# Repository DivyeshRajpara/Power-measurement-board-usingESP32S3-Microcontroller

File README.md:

# Power-measurement-board-usingESP32S3-Microcontroller
This project involves the development of a power-measurement board designed using KiCad and programmed with the ESP32-S3 microcontroller. The board measures electrical power and transmits the data via BLE to a mobile device. The project includes KiCad design files, ESP32-S3 firmware, and a mobile app interface for real-time data monitoring.
components
Hardware: KiCad design files for the power measurement board.
Firmware: ESP32-S3 code for data acquisition and BLE communication.
Devices: Interface for displaying real-time power data on a mobile device.
features
Power Measurement: Accurate measurement of voltage, current, and power.
Bluetooth Low Energy: Wireless data transmission to mobile devices.
ESP32-S3 Microcontroller: High-performance MCU with integrated Wi-Fi and BLE.
KiCad Design: Open-source PCB design with comprehensive schematics and layout files.

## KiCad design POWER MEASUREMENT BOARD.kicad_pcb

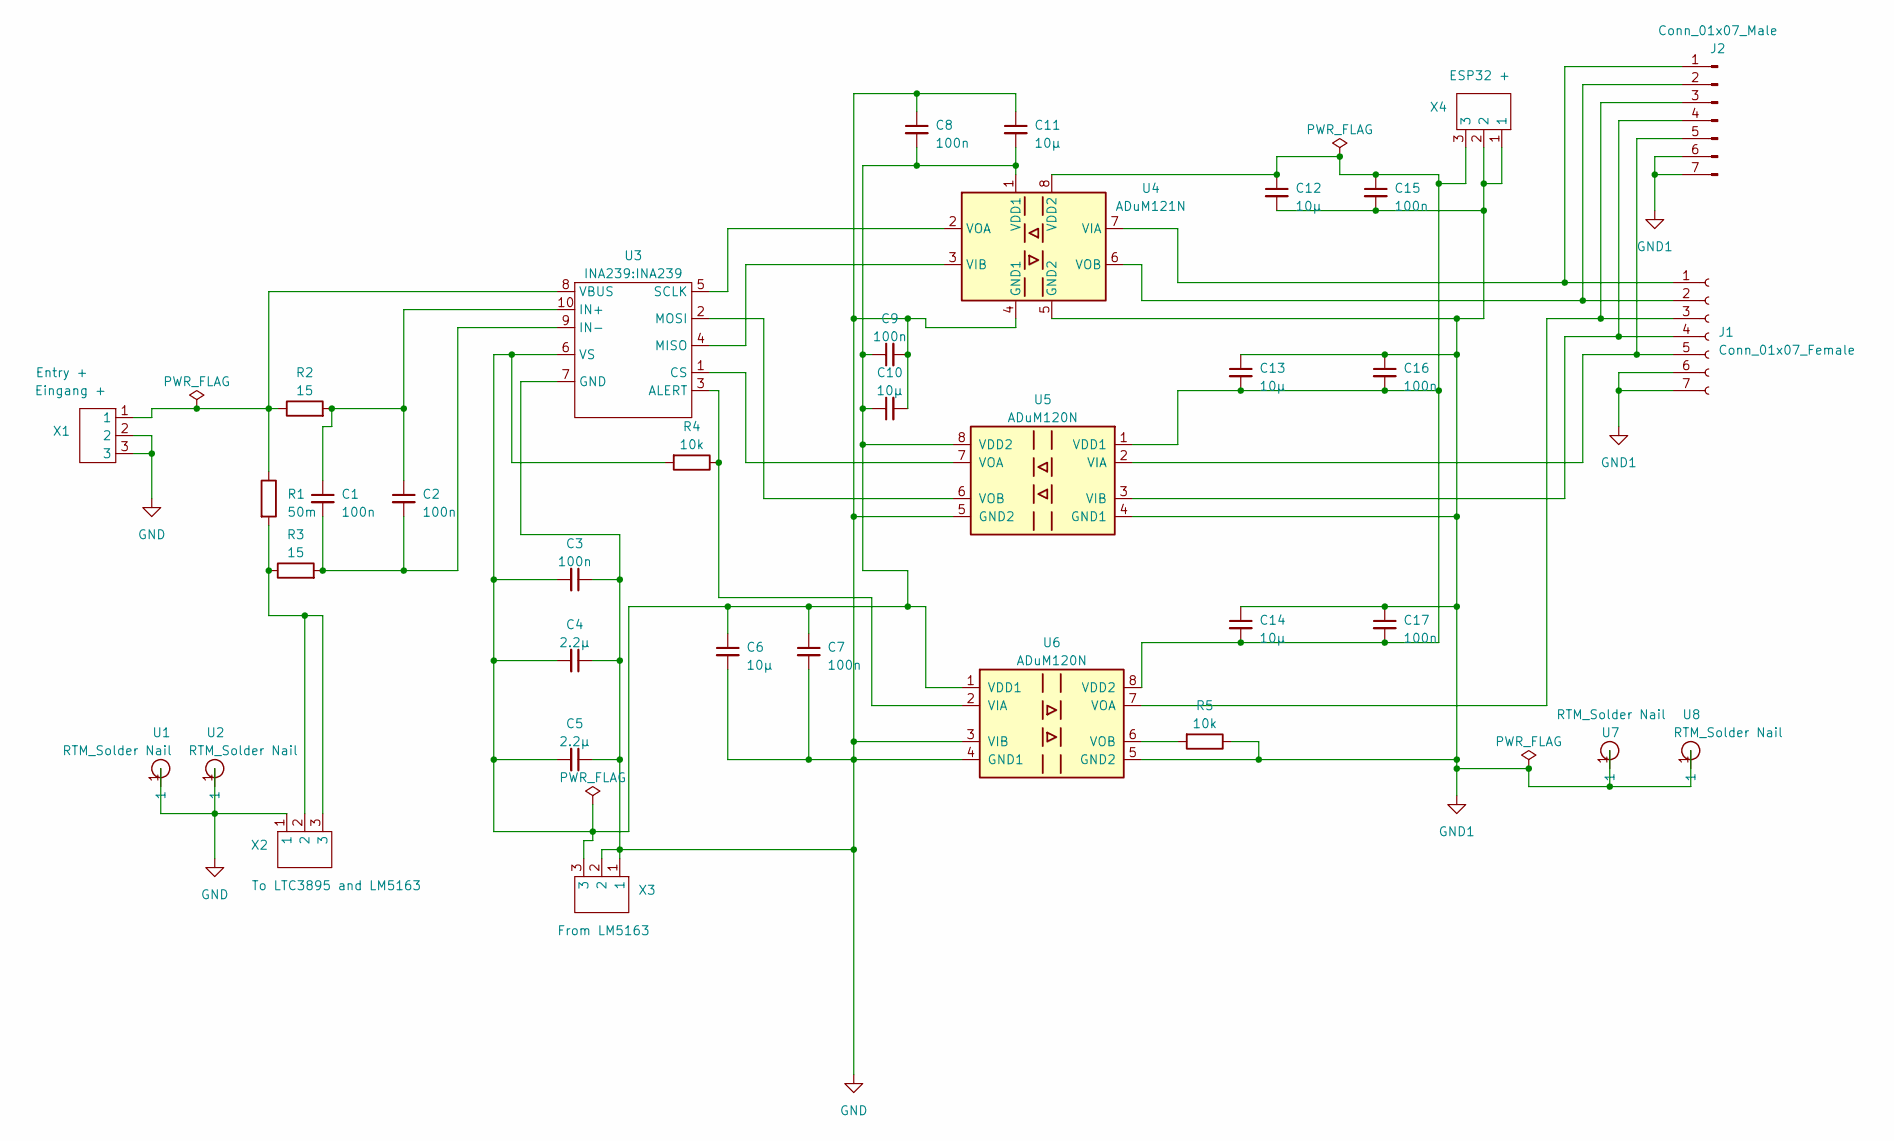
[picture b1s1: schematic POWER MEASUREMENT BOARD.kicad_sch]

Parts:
C1, C2, C15, C16, C17: 100n; C_0402_1005Metric_Pad0.74x0.62mm_HandSolder
C3, C7, C8, C9: 100n; C_0805_2012Metric_Pad1.18x1.45mm_HandSolder
C4, C5: 2.2μ; C_1206_3216Metric_Pad1.33x1.80mm_HandSolder
C6, C10, C11, C12, C13, C14: 10μ; C_1206_3216Metric_Pad1.33x1.80mm_HandSolder
J1: Conn_01x07_Female; PinSocket_1x07_P2.54mm_Vertical
J2: Conn_01x07_Male; PinHeader_1x07_P2.54mm_Vertical
R1: 50m; R_2010_5025Metric_Pad1.40x2.65mm_HandSolder
R2, R3: 15; R_0402_1005Metric_Pad0.72x0.64mm_HandSolder
R4, R5: 10k; R_0402_1005Metric_Pad0.72x0.64mm_HandSolder
U1, U2, U7, U8: RTM_Solder Nail
U3: INA239
U4: ADuM121N; SOIC-8_3.9x4.9mm_P1.27mm
U5, U6: ADuM120N; SOIC-8_3.9x4.9mm_P1.27mm
X1: Eingang +
X2: To LTC3895 and LM5163
X3: From LM5163
X4: ESP32 +

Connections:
GND: C3.1, C4.1, C5.1, C6.2, C7.2, C8.1, C9.2, C10.2, C11.1, U1.1, U2.1, U3.7 (GND), U4.4 (GND1), U5.5 (GND2), U6.3 (VIB), U6.4 (GND1), X1.2, X1.3, X2.1, X3.1, X3.2
GND1: C12.2, C13.1, C14.1, C15.2, C16.1, C17.1, J1.6, J1.7, J2.6, J2.7, R5.1, U4.5 (GND2), U5.4 (GND1), U6.5 (GND2), U7.1, U8.1, X4.1, X4.2
unnamed: J1.1, J2.1, U4.7 (VIA)
unnamed: J1.2, J2.2, U4.6 (VOB)
unnamed: J1.3, J2.3, U6.7 (VOA)
unnamed: J1.4, J2.4, U5.3 (VIB)
unnamed: J1.5, J2.5, U5.2 (VIA)
unnamed: R1.2, R3.1, X2.2, X2.3
unnamed: R4.1, U3.3 (ALERT), U6.2 (VIA)
unnamed: U3.1 (CS), U5.7 (VOA)
unnamed: C1.1, C2.1, R2.2, U3.10 (IN+)
unnamed: C1.2, C2.2, R3.2, U3.9 (IN-)
unnamed: U3.4 (MISO), U4.3 (VIB)
unnamed: U3.2 (MOSI), U5.6 (VOB)
unnamed: U3.5 (SCLK), U4.2 (VOA)
unnamed: R1.1, R2.1, U3.8 (VBUS), X1.1
unnamed: C3.2, C4.2, C5.2, C6.1, C7.1, C8.2, C9.1, C10.1, C11.2, R4.2, U3.6 (VS), U4.1 (VDD1), U5.8 (VDD2), U6.1 (VDD1), X3.3
unnamed: C12.1, C13.2, C14.2, C15.1, C16.2, C17.2, U4.8 (VDD2), U5.1 (VDD1), U6.8 (VDD2), X4.3
unnamed: R5.2, U6.6 (VOB)

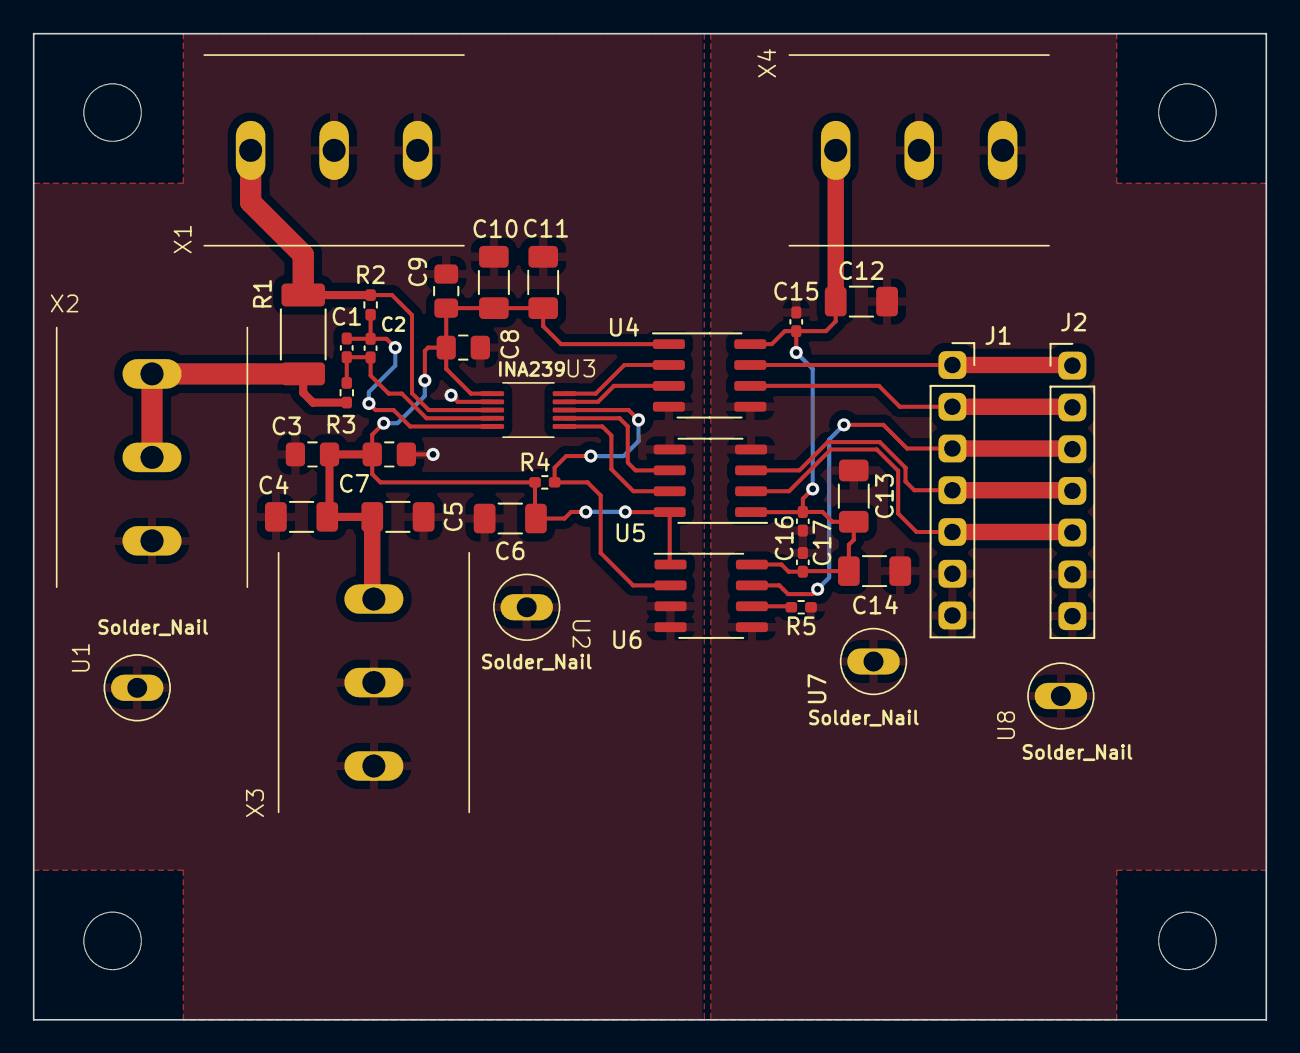
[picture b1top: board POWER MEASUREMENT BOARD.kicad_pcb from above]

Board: 2 copper layers, 75.0 x 60.0 mm, 36 parts (0 on the bottom side), 19 nets.

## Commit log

2024-07-31 Create ESP32S3 microcontroller programing
